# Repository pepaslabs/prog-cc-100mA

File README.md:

# prog-cc-100mA
A programmable 100mA current source

# Status

This board has been tested and works.

With cheap components, it makes a decent low-precision current source.  I'm currently awaiting the arrival of some low temperature coefficient resistors and low input offset voltage opamps to see if performance can be improved.

# Board design v1

Initial board design.

## Gerbers

[gerbers.zip](kicad/releases/v1/gerbers.zip)

## Schematic

[PDF](kicad/releases/v1/prog-cc-100mA-schematic.pdf).

# License

This board design is [Open-Source Hardware](http://www.oshwa.org/definition/).  It is licensed under the [MIT License](http://opensource.org/licenses/MIT).  It was designed by Jason Pepas.

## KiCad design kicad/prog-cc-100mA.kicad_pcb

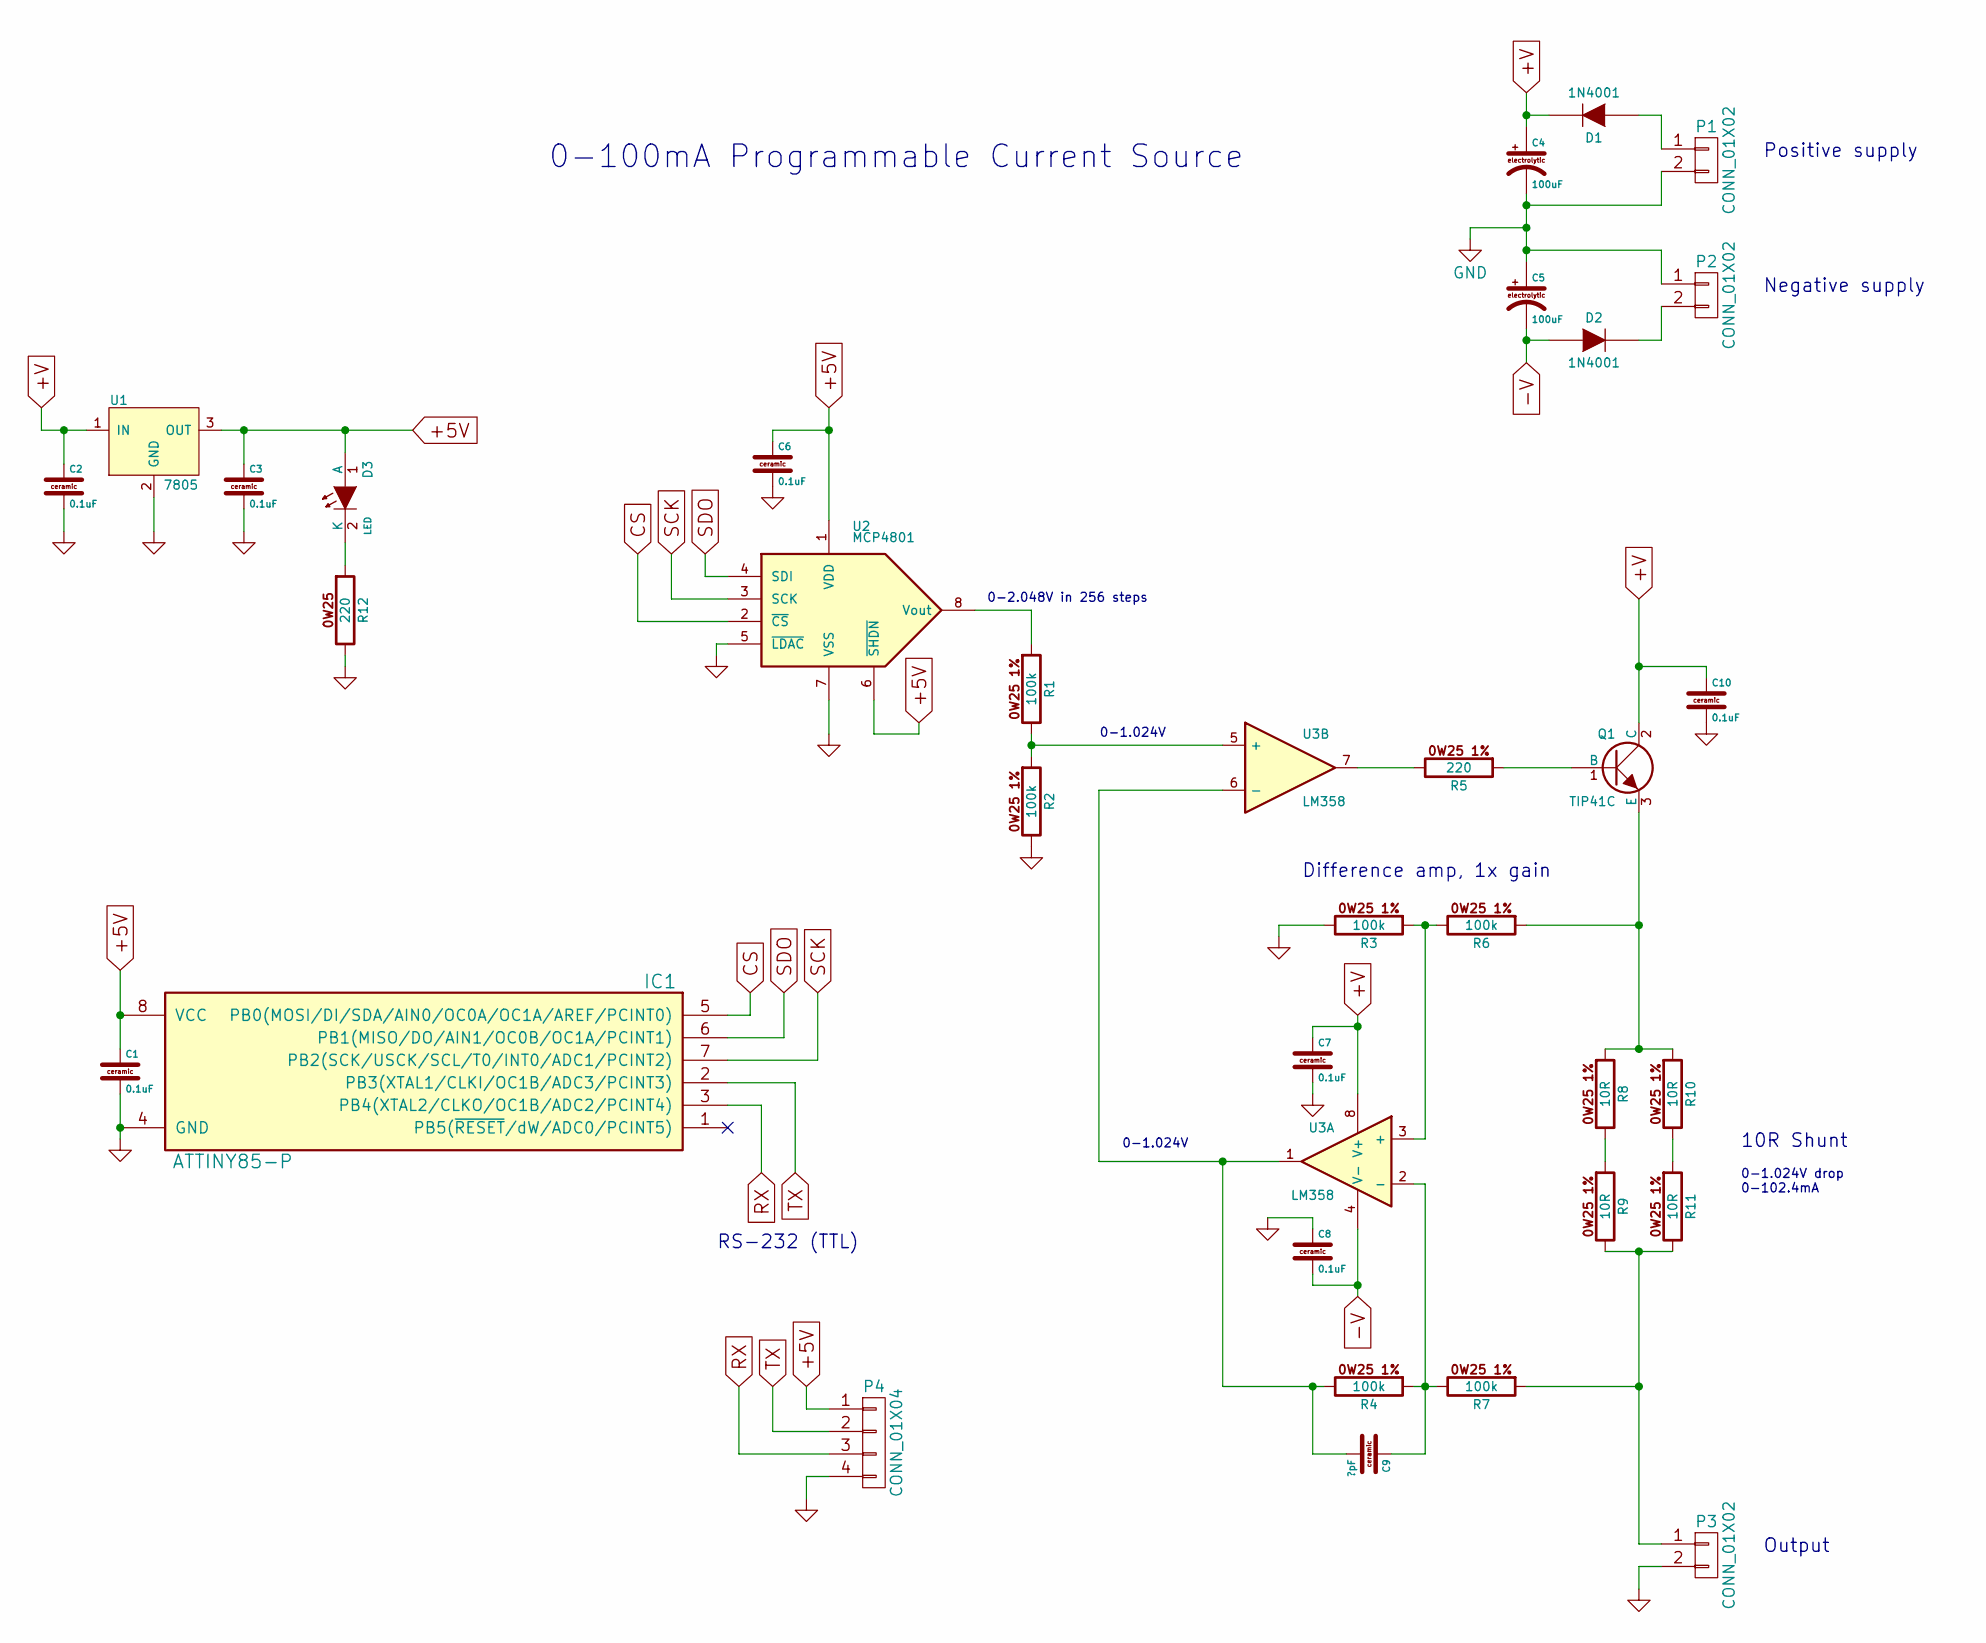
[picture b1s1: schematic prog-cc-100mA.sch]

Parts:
C1, C2, C3, C6, C7, C8, C10: 0.1uF; CERCAP_2_059B_0805
C4, C5: 100uF; ELCAP_10_20_V_059A
C9: ?pF; CERCAP_2_059B_0805
D1, D2: 1N4001; DIODE_1A_069A_PL
D3: LED; LED_3MM_069A
IC1: ATTINY85-P; DIP8_059A_PL
P1, P2, P3: CONN_01X02; Pin_Header_Straight_1x02
P4: CONN_01X04; Pin_Header_Straight_1x04
Q1: TIP41C; TO-220_V_069A
R1, R2, R3, R4, R6, R7: 100k; R_AXIAL_0W25_059A_PL
R5, R12: 220; R_AXIAL_0W25_059A_PL
R8, R9, R10, R11: 10R; R_AXIAL_0W25_059A_PL
U1: 7805; TO-220_V_069A
U2: MCP4801; DIP8_059A_PL
U3: LM358; DIP8_059A_PL

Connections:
+5V: C1.1, C3.1, C6.1, D3.1 (A), IC1.8 (VCC), P4.1, U1.3 (OUT), U2.1 (VDD), U2.6 (~SHDN~)
+V: C2.1, C4.1, C7.1, C10.1, D1.2 (K), Q1.2 (C), U1.1 (IN), U3.8 (V+)
-V: C5.2, C8.2, D2.1 (A), U3.4 (V-)
CS: IC1.5 (PB0(MOSI/DI/SDA/AIN0/OC0A/OC1A/AREF/PCI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), U2.2 (~CS~)
GND: C1.2, C2.2, C3.2, C4.2, C5.1, C6.2, C7.2, C8.1, C10.2, IC1.4 (GND), P1.2, P2.1, P3.2, P4.4, R2.2, R3.2, R12.2, U1.2 (GND), U2.5 (~LDAC~), U2.7 (VSS)
unnamed: C9.1, R4.1, R7.2, U3.2 (-)
unnamed: C9.2, R4.2, U3.1, U3.6 (-)
unnamed: D1.1 (A), P1.1
unnamed: D2.2 (K), P2.2
unnamed: D3.2 (K), R12.1
unnamed: Q1.1 (B), R5.1
unnamed: Q1.3 (E), R6.1, R8.1, R10.1
unnamed: R1.1, U2.8 (Vout)
unnamed: R1.2, R2.1, U3.5 (+)
unnamed: R3.1, R6.2, U3.3 (+)
unnamed: R5.2, U3.7
unnamed: R8.2, R9.1
unnamed: R10.2, R11.1
Out: P3.1, R7.1, R9.2, R11.2
RX: IC1.3 (PB4(XTAL2/CLKO/OC1B/ADC2/PCINT4)), P4.3
SCK: IC1.7 (PB2(SCK/USCK/SCL/T0/INT0/ADC1/PCINT2)), U2.3 (SCK)
SDO: IC1.6 (PB1(MISO/DO/AIN1/OC0B/OC1A/PCINT1)), U2.4 (SDI)
TX: IC1.2 (PB3(XTAL1/CLKI/OC1B/ADC3/PCINT3)), P4.2

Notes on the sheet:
10R Shunt
Difference amp, 1x gain
RS-232 (TTL)
0-2.048V in 256 steps
0-1.024V
0-1.024V drop 0-102.4mA
0-100mA Programmable Current Source
Output
Positive supply
Negative supply

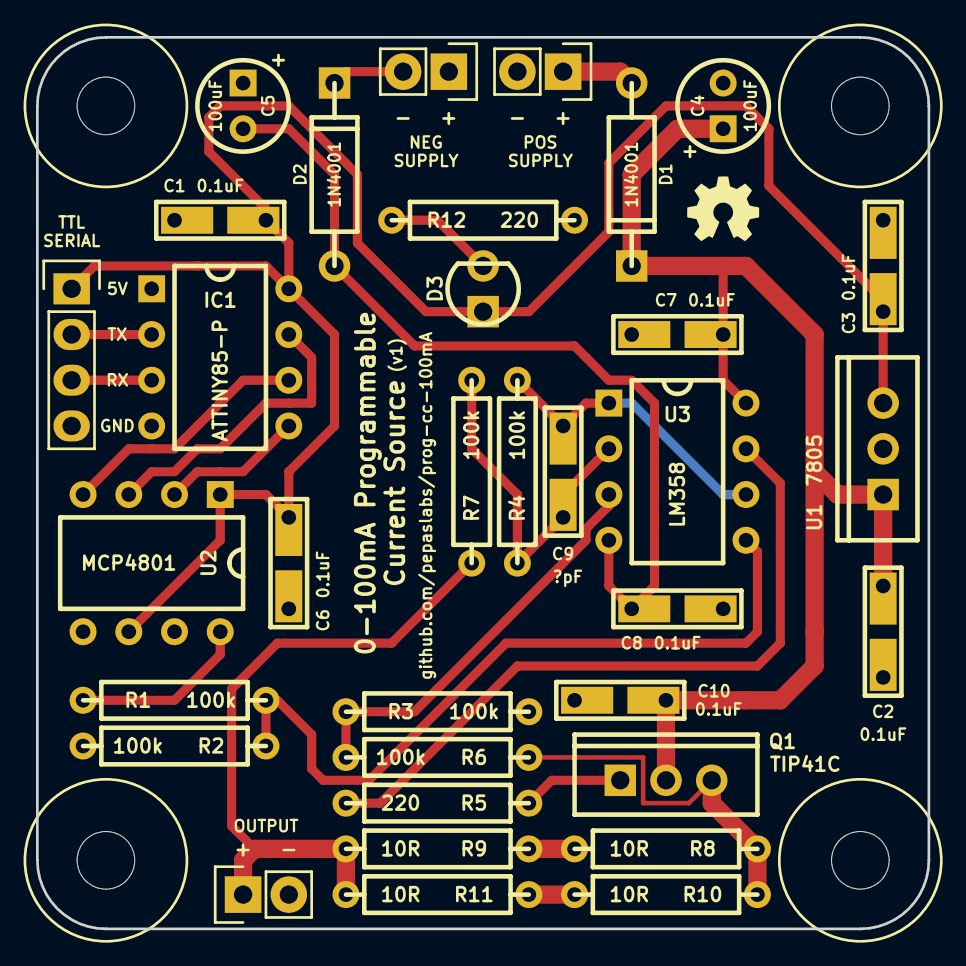
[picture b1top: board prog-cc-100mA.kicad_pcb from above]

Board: 2 copper layers, 49.5 x 49.5 mm, 38 parts (0 on the bottom side), 23 nets.

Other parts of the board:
H***: Val**; hole_M3_NPTH
H***#2, H***#3, H***#4: Val**; hole_M3_NPTH

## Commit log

2017-04-20 Initial release (v1 board design)
2017-04-20 Adding schematic pdf
2017-04-20 Tweaking PCB text layout
2017-04-20 Adding PCB renders
2017-04-22 moving schematic
2017-05-10 cleaning bak files
2017-05-10 Tweaking a few part designations
2017-05-11 Adding resistor matching scripts
2017-05-11 firmware for ATtiny85
2017-05-12 fixing a math error
2017-05-13 adding board shots
2017-05-14 adapting firmware from pepaslabs/ProgrammableLM317
2017-05-14 consolidating strings to save a bit of SRAM
2017-05-14 print the DAC code after every command
2017-05-14 tweaks
2017-05-20 rotating schematic
